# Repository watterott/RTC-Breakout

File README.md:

# RTC-Breakout
Breakout with Micro Crystal RV-8523-C3 RTC (Real-Time-Clock) and CR1225 Battery.

* Ultra Low Power Consumption
* Integrated Crystal
* I2C/TWI Interface (fast mode 1 MHz, address 0xD0)
* Compatible with NXP PCF8523
* Power Supply: 1.8 - 5V
* Open-Source and released under the [Creative Commons Attribution Share-Alike License](https://creativecommons.org/licenses/by-sa/4.0/).
* **[Documentation on learn.watterott.com](https://learn.watterott.com)**

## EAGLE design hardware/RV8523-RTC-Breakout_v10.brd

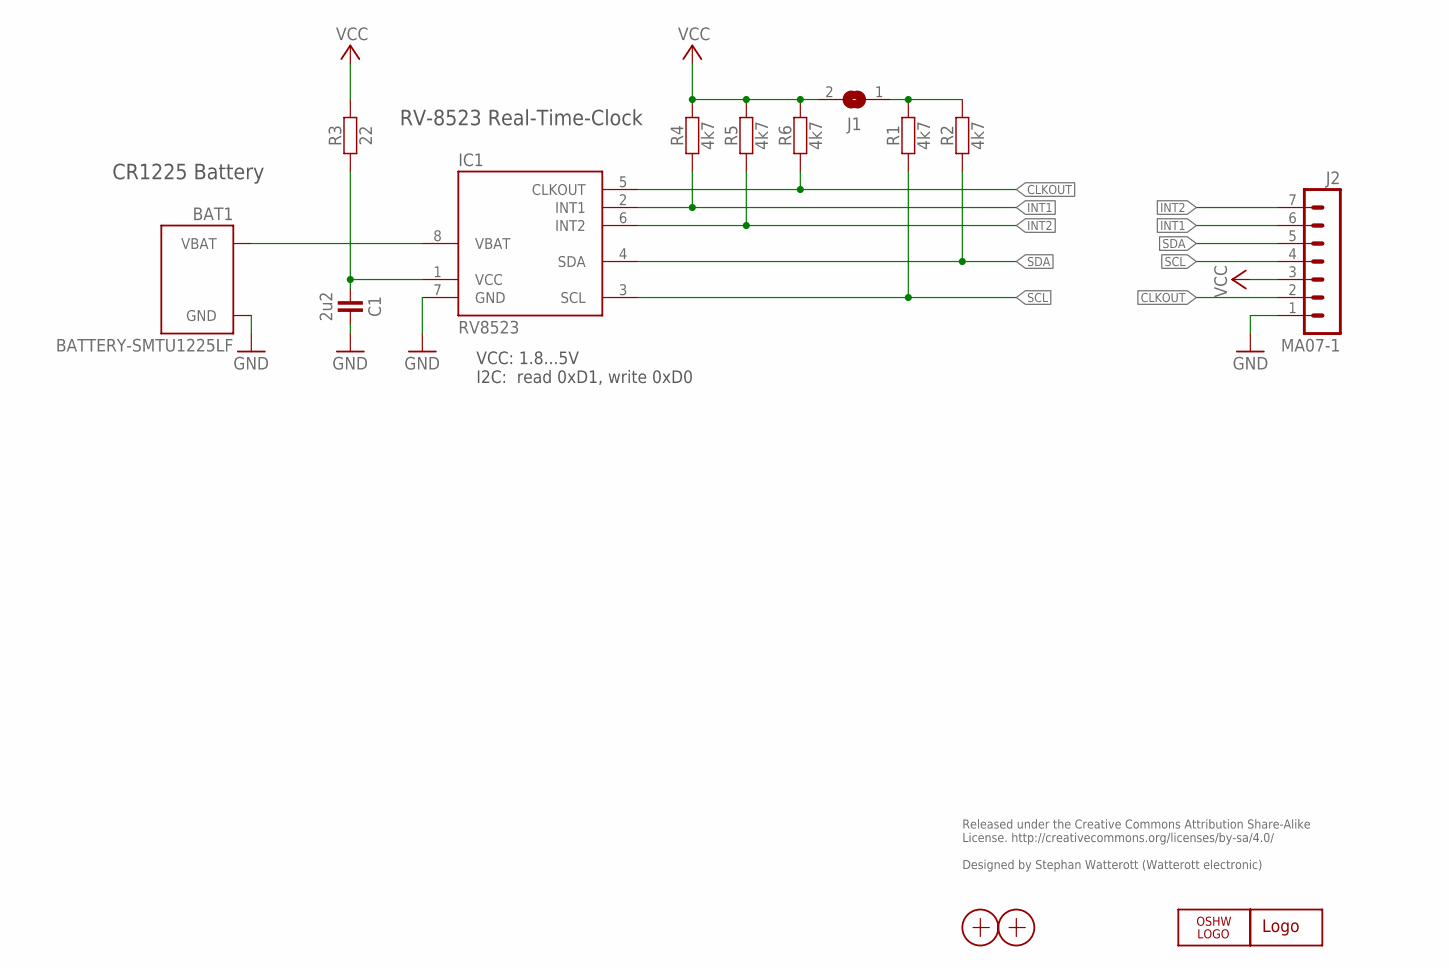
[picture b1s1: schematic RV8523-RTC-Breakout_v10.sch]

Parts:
BAT1: BATTERY-SMTU1225LF; BAT-SMTU1225LF
C1: 2u2; R0603
IC1: RV8523; RTC-C3
J1: JUMPER2
J2: MA07-1
LOGO1: LOGO-S_PLACE_M; SPARK_TPLACE_M
LOGO2: OSHW_LOGOX0070; OSHW_6X70
R1, R2, R4, R5, R6: 4k7; R0603
R3: 22; R0603
X1, X2: PASSER-07; PASSER_07MM

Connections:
CLKOUT: IC1.5 (CLKOUT), J2.2, R6.1
GND: BAT1.- (GND), C1.2, IC1.7 (GND), J2.1
I2C_VCC: J1.1, R1.2, R2.2
INT1: IC1.2 (INT1), J2.6, R4.1
INT2: IC1.6 (INT2), J2.7, R5.1
RV_VCC: C1.1, IC1.1 (VCC), R3.1
SCL: IC1.3 (SCL), J2.4, R1.1
SDA: IC1.4 (SDA), J2.5, R2.1
VBAT: BAT1.+ (VBAT), IC1.8 (VBAT)
VCC: J1.2, J2.3, R3.2, R4.2, R5.2, R6.2

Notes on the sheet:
Released under the Creative Commons Attribution Share-Alike License. http://creativecommons.org/licenses/by-sa/4.0/ Designed by Stephan Watterott (Watterott electronic)
VCC: 1.8...5V I2C: read 0xD1, write 0xD0
RV-8523 Real-Time-Clock
CR1225 Battery

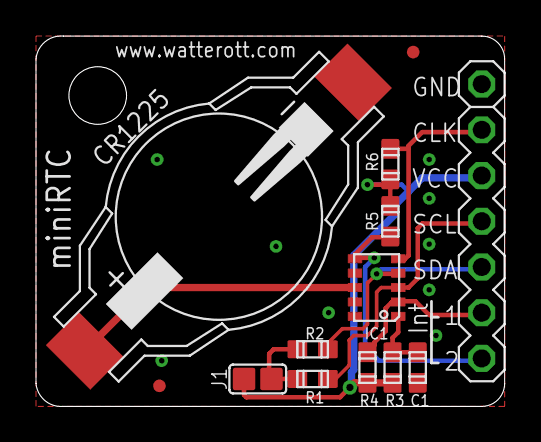
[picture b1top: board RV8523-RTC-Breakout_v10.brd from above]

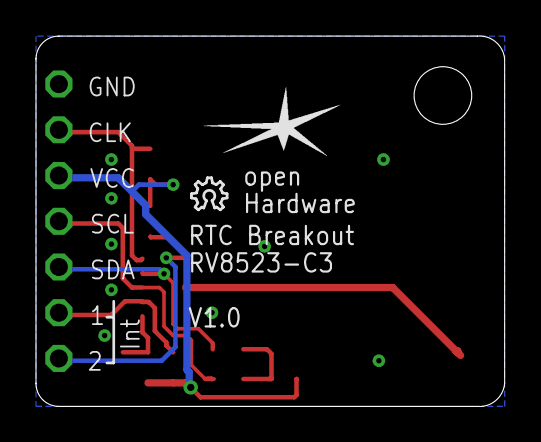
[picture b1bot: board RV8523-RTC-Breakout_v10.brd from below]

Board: 2 copper layers, 26.0 x 20.6 mm, 15 parts (2 on the bottom side), 10 nets.

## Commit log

2020-05-16 updated example
